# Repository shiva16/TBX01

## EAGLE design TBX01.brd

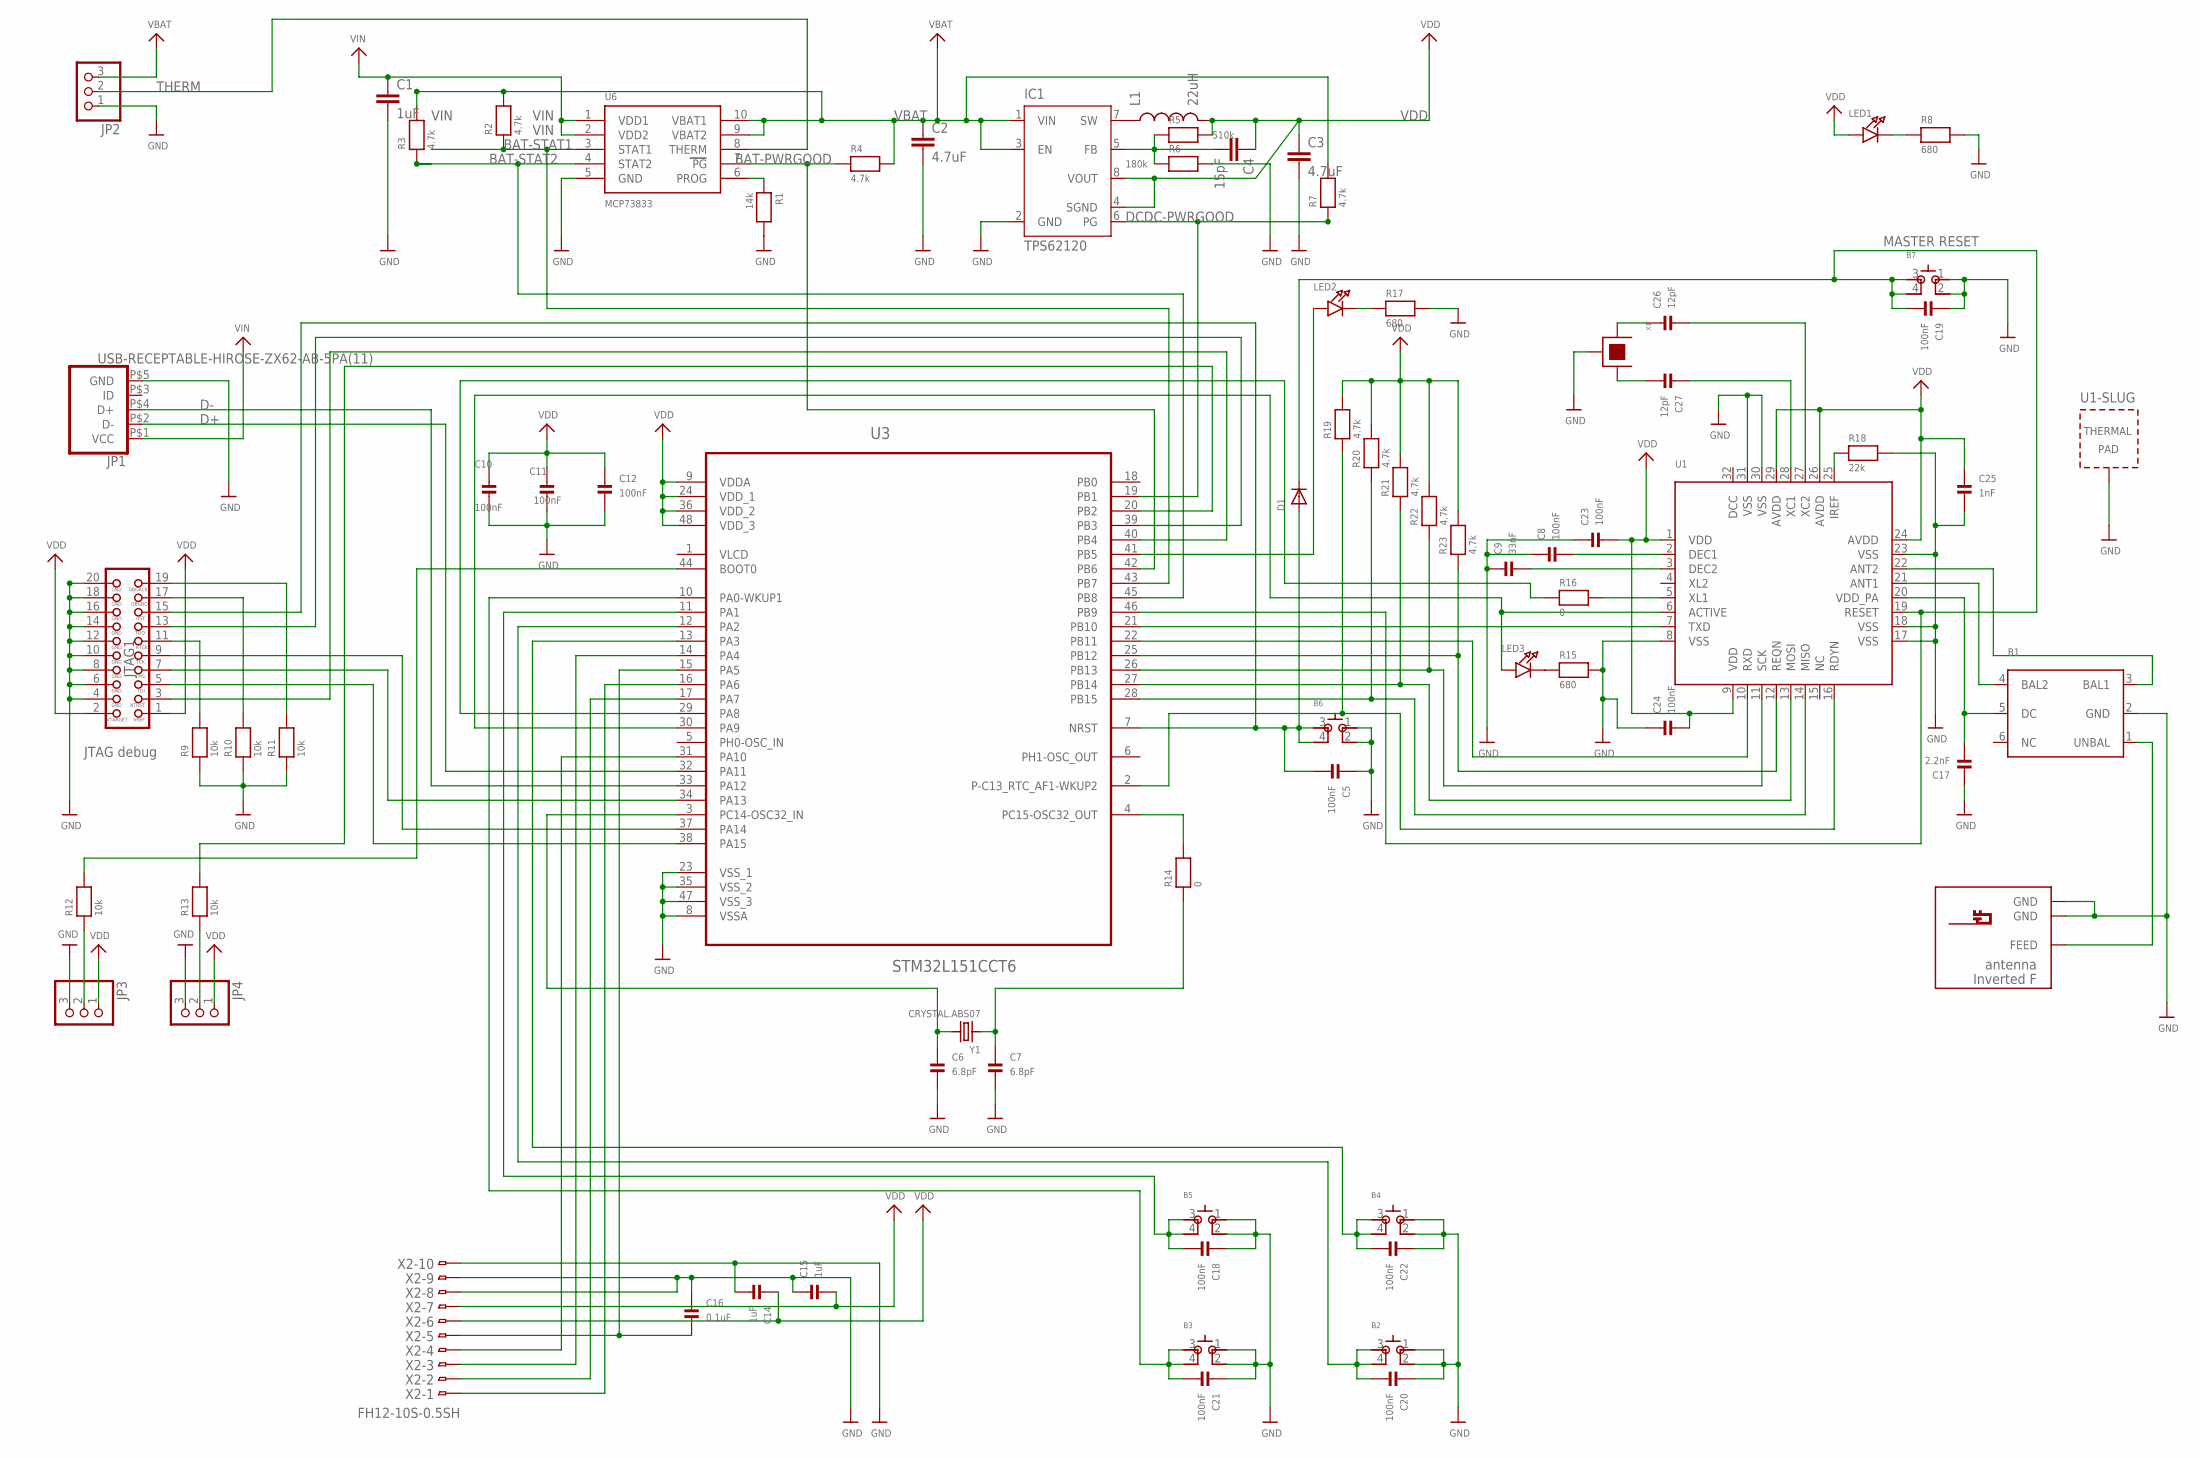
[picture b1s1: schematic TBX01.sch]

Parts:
B1: BALUN+LP_NORDIC; BALUN0603
B2, B3, B4, B5, B6, B7: SKSCLDE010
C1: 1uF; C0603
C2, C3: 4.7uF; C0603
C4: 15pF; C0603
C5, C8, C10, C11, C12, C18, C19, C20, C21, C22, C23, C24: 100nF; 0603
C6, C7: 6.8pF; 0603
C9: 33nF; 0603
C14, C15: 1uF; 0603
C16: 0.1uF; 0603
C17: 2.2nF; 0603
C25: 1nF; 0603
C26, C27: 12pF; 0603
D1: DIODESOD-123; SOD-123
IC1: TPS62120; DCN-R-PDSO-G8
JP1: USB-RECEPTABLE-HIROSE-ZX62-AB-5PA(11); HIROSE-ZX62-AB-5PA(11)
JP2, JP3, JP4: HEADER-1X3ROUND; 1X03_ROUND
JTAG1: JTAG-ARM
L1: 22uH; 1210
LED1, LED2, LED3: LED0603; CHIPLED_0603
R1: 14k; 0603
R2, R3, R4, R7, R19, R20, R21, R22, R23: 4.7k; 0603
R5: 510k; 0603
R6: 180k; 0603
R8, R15, R17: 680; 0603
R9, R10, R11, R12, R13: 10k; 0603
R14, R16: 0; 0603
R18: 22k; 0603
U1: NRF8001; QFN32_5MM
U3: STM32L151CCT6; QFP50P900X900X160-48N
U6: MCP73833; MSOP10
U$44: INVERTED_F_ANTENNA+0; DN007+0
X1: SHIELDED_CRYSTALTSX-3225; TSX-3225
X2: FH12-10S-0.5SH
Y1: CRYSTAL.ABS07; ABS07

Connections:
BAT-PWRGOOD: R4.1, U3.42 (PB6), U6.7 (PG)
BAT-STAT1: R2.1, U3.43 (PB7), U6.3 (STAT1)
BAT-STAT2: R3.1, U3.45 (PB8), U6.4 (STAT2)
D+: JP1.P$4 (D+), U3.33 (PA12)
D-: JP1.P$2 (D-), U3.32 (PA11)
DCDC-PWRGOOD: IC1.6 (PG), R7.1, U3.19 (PB1)
GND: B1.2 (GND), B2.1 (4), B2.2 (3), B3.1 (4), B3.2 (3), B4.1 (4), B4.2 (3), B5.1 (4), B5.2 (3), B6.1 (4), B6.2 (3), B7.1 (4), B7.2 (3), C1.2, C2.2, C3.2, C5.1, C6.2, C7.2, C8.1, C9.1, C10.2, C11.1, C12.2, C14.2, C15.1, C16.1, C17.1, C18.1, C19.1, C20.1, C21.1, C22.1, C23.1, C24.1, C25.2, IC1.2 (GND), JP1.P$5 (GND), JP2.1, JP3.3, JP4.3, JTAG1.4, JTAG1.6, JTAG1.8, JTAG1.10, JTAG1.12, JTAG1.14, JTAG1.16, JTAG1.18, JTAG1.20, R1.2, R6.2, R8.2, R9.1, R10.1, R11.1, R15.2, R17.2, R18.2, U1.8 (VSS), U1.17 (VSS), U1.18 (VSS), U1.23 (VSS), U1.30 (VSS), U1.31 (VSS), U1.GND (TP), U3.8 (VSSA), U3.23 (VSS_1), U3.35 (VSS_2), U3.47 (VSS_3), U6.5 (GND), U$44.GND, U$44.GND@1 (GND), X1.2, X1.4, X2.8, X2.9, X2.10
unnamed: R1.1, U6.6 (PROG)
unnamed: LED1.C, R8.1
unnamed: C4.2, IC1.5 (FB), R5.1, R6.1
unnamed: IC1.7 (SW), L1.1
unnamed: JTAG1.3, U3.40 (PB4)
unnamed: JTAG1.13, U3.39 (PB3)
unnamed: JTAG1.5, U3.38 (PA15)
unnamed: JTAG1.7, U3.34 (PA13)
unnamed: JTAG1.9, U3.37 (PA14)
unnamed: B7.3 (1), B7.4 (2), C19.2, D1.C, U1.19 (RESET), U3.46 (PB9)
unnamed: JTAG1.11, R9.2
unnamed: JTAG1.17, R10.2
unnamed: JTAG1.19, R11.2
unnamed: JP3.2, R12.1
unnamed: JP4.2, R13.1
unnamed: R12.2, U3.44 (BOOT0)
unnamed: R13.2, U3.20 (PB2)
unnamed: C6.1, U3.3 (PC14-OSC32_IN), Y1.2
unnamed: C8.2, U1.2 (DEC1)
unnamed: C9.2, U1.3 (DEC2)
unnamed: R14.2, U3.4 (PC15-OSC32_OUT)
unnamed: C7.1, R14.1, Y1.1
unnamed: LED3.A, U1.6 (ACTIVE), U3.30 (PA9)
unnamed: C16.2, U3.15 (PA5), X2.5
unnamed: U3.31 (PA10), X2.4
unnamed: U3.14 (PA4), X2.3
unnamed: U3.17 (PA7), X2.2
unnamed: U3.16 (PA6), X2.1
unnamed: R16.1, U3.29 (PA8)
unnamed: U1.7 (TXD), U3.21 (PB10)
unnamed: U1.10 (RXD), U3.22 (PB11)
unnamed: R22.1, U1.11 (SCK), U3.26 (PB13)
unnamed: R23.1, U1.12 (REQN), U3.25 (PB12)
unnamed: R21.1, U1.13 (MOSI), U3.27 (PB14)
unnamed: R20.1, U1.14 (MISO), U3.28 (PB15)
unnamed: R19.1, U1.16 (RDYN), U3.2 (P-C13_RTC_AF1-WKUP2)
unnamed: LED3.C, R15.1
unnamed: B3.3 (1), B3.4 (2), C21.2, U3.10 (PA0-WKUP1)
unnamed: R16.2, U1.5 (XL1)
unnamed: B5.3 (1), B5.4 (2), C18.2, U3.11 (PA1)
unnamed: B2.3 (1), B2.4 (2), C20.2, U3.12 (PA2)
unnamed: B4.3 (1), B4.4 (2), C22.2, U3.13 (PA3)
unnamed: LED2.A, U3.41 (PB5)
unnamed: LED2.C, R17.1
unnamed: B1.4 (BAL2), U1.21 (ANT1)
unnamed: B1.3 (BAL1), U1.22 (ANT2)
unnamed: B1.1 (UNBAL), U$44.FEED
unnamed: B1.5 (DC), C17.2, U1.20 (VDD_PA)
unnamed: R18.1, U1.25 (IREF)
unnamed: C26.1, X1.1
unnamed: C27.2, X1.3
unnamed: C27.1, U1.28 (XC1)
unnamed: C26.2, U1.27 (XC2)
unnamed: B6.3 (1), B6.4 (2), C5.2, D1.A, JTAG1.15, U3.7 (NRST)
THERM: JP2.2, U6.8 (THERM)
VBAT: C2.1, IC1.1 (VIN), IC1.3 (EN), JP2.3, R2.2, R3.2, R4.2, R7.2, U6.9 (VBAT2), U6.10 (VBAT1)
VDD: C3.1, C4.1, C10.1, C11.2, C12.1, C14.1, C15.2, C23.2, C24.2, C25.1, IC1.4 (SGND), IC1.8 (VOUT), JP3.1, JP4.1, JTAG1.1, JTAG1.2, L1.2, LED1.A, R5.2, R19.2, R20.2, R21.2, R22.2, R23.2, U1.1 (VDD), U1.9 (VDD), U1.24 (AVDD), U1.26 (AVDD), U1.29 (AVDD), U3.9 (VDDA), U3.24 (VDD_1), U3.36 (VDD_2), U3.48 (VDD_3), X2.6, X2.7
VIN: C1.1, JP1.P$1 (VCC), U6.1 (VDD1), U6.2 (VDD2)
VLCD: U3.1 (VLCD)

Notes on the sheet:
JTAG debug
MASTER RESET

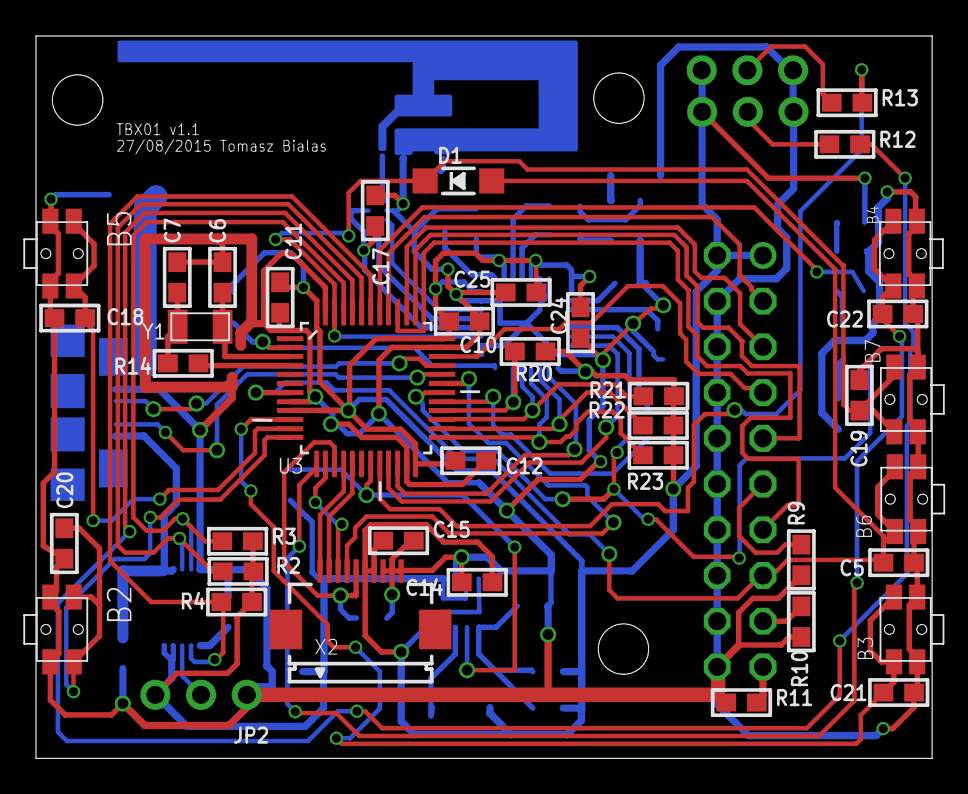
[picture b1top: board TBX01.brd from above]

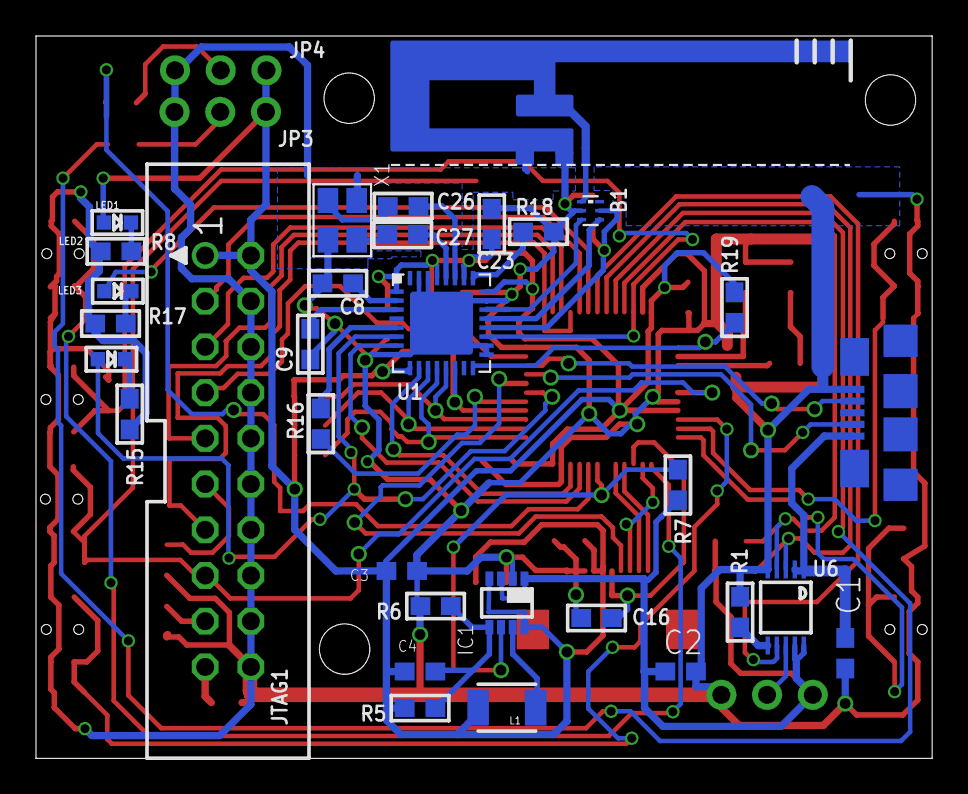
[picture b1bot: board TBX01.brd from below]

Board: 2 copper layers, 49.8 x 40.1 mm, 74 parts (33 on the bottom side), 65 nets.

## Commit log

2015-08-15 TBX01 v0.1
2015-08-17 TBX01 v0.2
2015-08-17 TBX01 v0.2-r201508171545
    On branch master
    .~lock.TBX-01_power.ods#
    nothing added to commit but untracked files present (use "git add" to track)
2015-08-17 TBX01 v0.2-r201508171633
2015-08-17 TBX01 v0.2-r201508172343
2015-08-18 TBX01 v0.2-r201508181539
2015-08-18 TBX01 v0.2-r201508181630
2015-08-18 TBX01 v0.2-r201508190105
2015-08-19 TBX01 v0.2-r201508191318
    Before nRF8001 move left
2015-08-20 TBX01 v0.2-r201508201349
2015-08-20 TBX01 v0.2-r201508201530
2015-08-20 TBX01 v0.2-r201508201618
2015-08-21 TBX01 v0.3
    Button update
2015-08-21 TBX01 v0.3-r201508201530
2015-08-22 TBX01 v0.3-r201508230020
2015-08-22 TBX01 v0.3-r201508230138
2015-08-23 TBX01 v0.3-r201508231801
2015-08-24 TBX01 v0.3-r201508240212
2015-08-24 TBX01 v0.3-r201508241143
2015-08-24 TBX01 v0.4
2015-08-24 TBX01 v0.4-r201508241723
2015-08-24 TBX01 v0.5
2015-08-27 TBX01 v0.6
2015-08-27 TBX01 v0.7
2015-08-27 TBX01 v1.0
2015-10-20 TBX01 v1.0-r201510201242
2015-10-22 TBX01 v1.1

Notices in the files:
parts and their libraries:
microbuilder: This work is placed in the public domain, and may be freely used for commercial and non-commercial work with the following conditions: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
SparkFun-Passives: Licensing: Creative Commons ShareAlike 4.0 International - https://creativecommons.org/licenses/by-sa/4.0
